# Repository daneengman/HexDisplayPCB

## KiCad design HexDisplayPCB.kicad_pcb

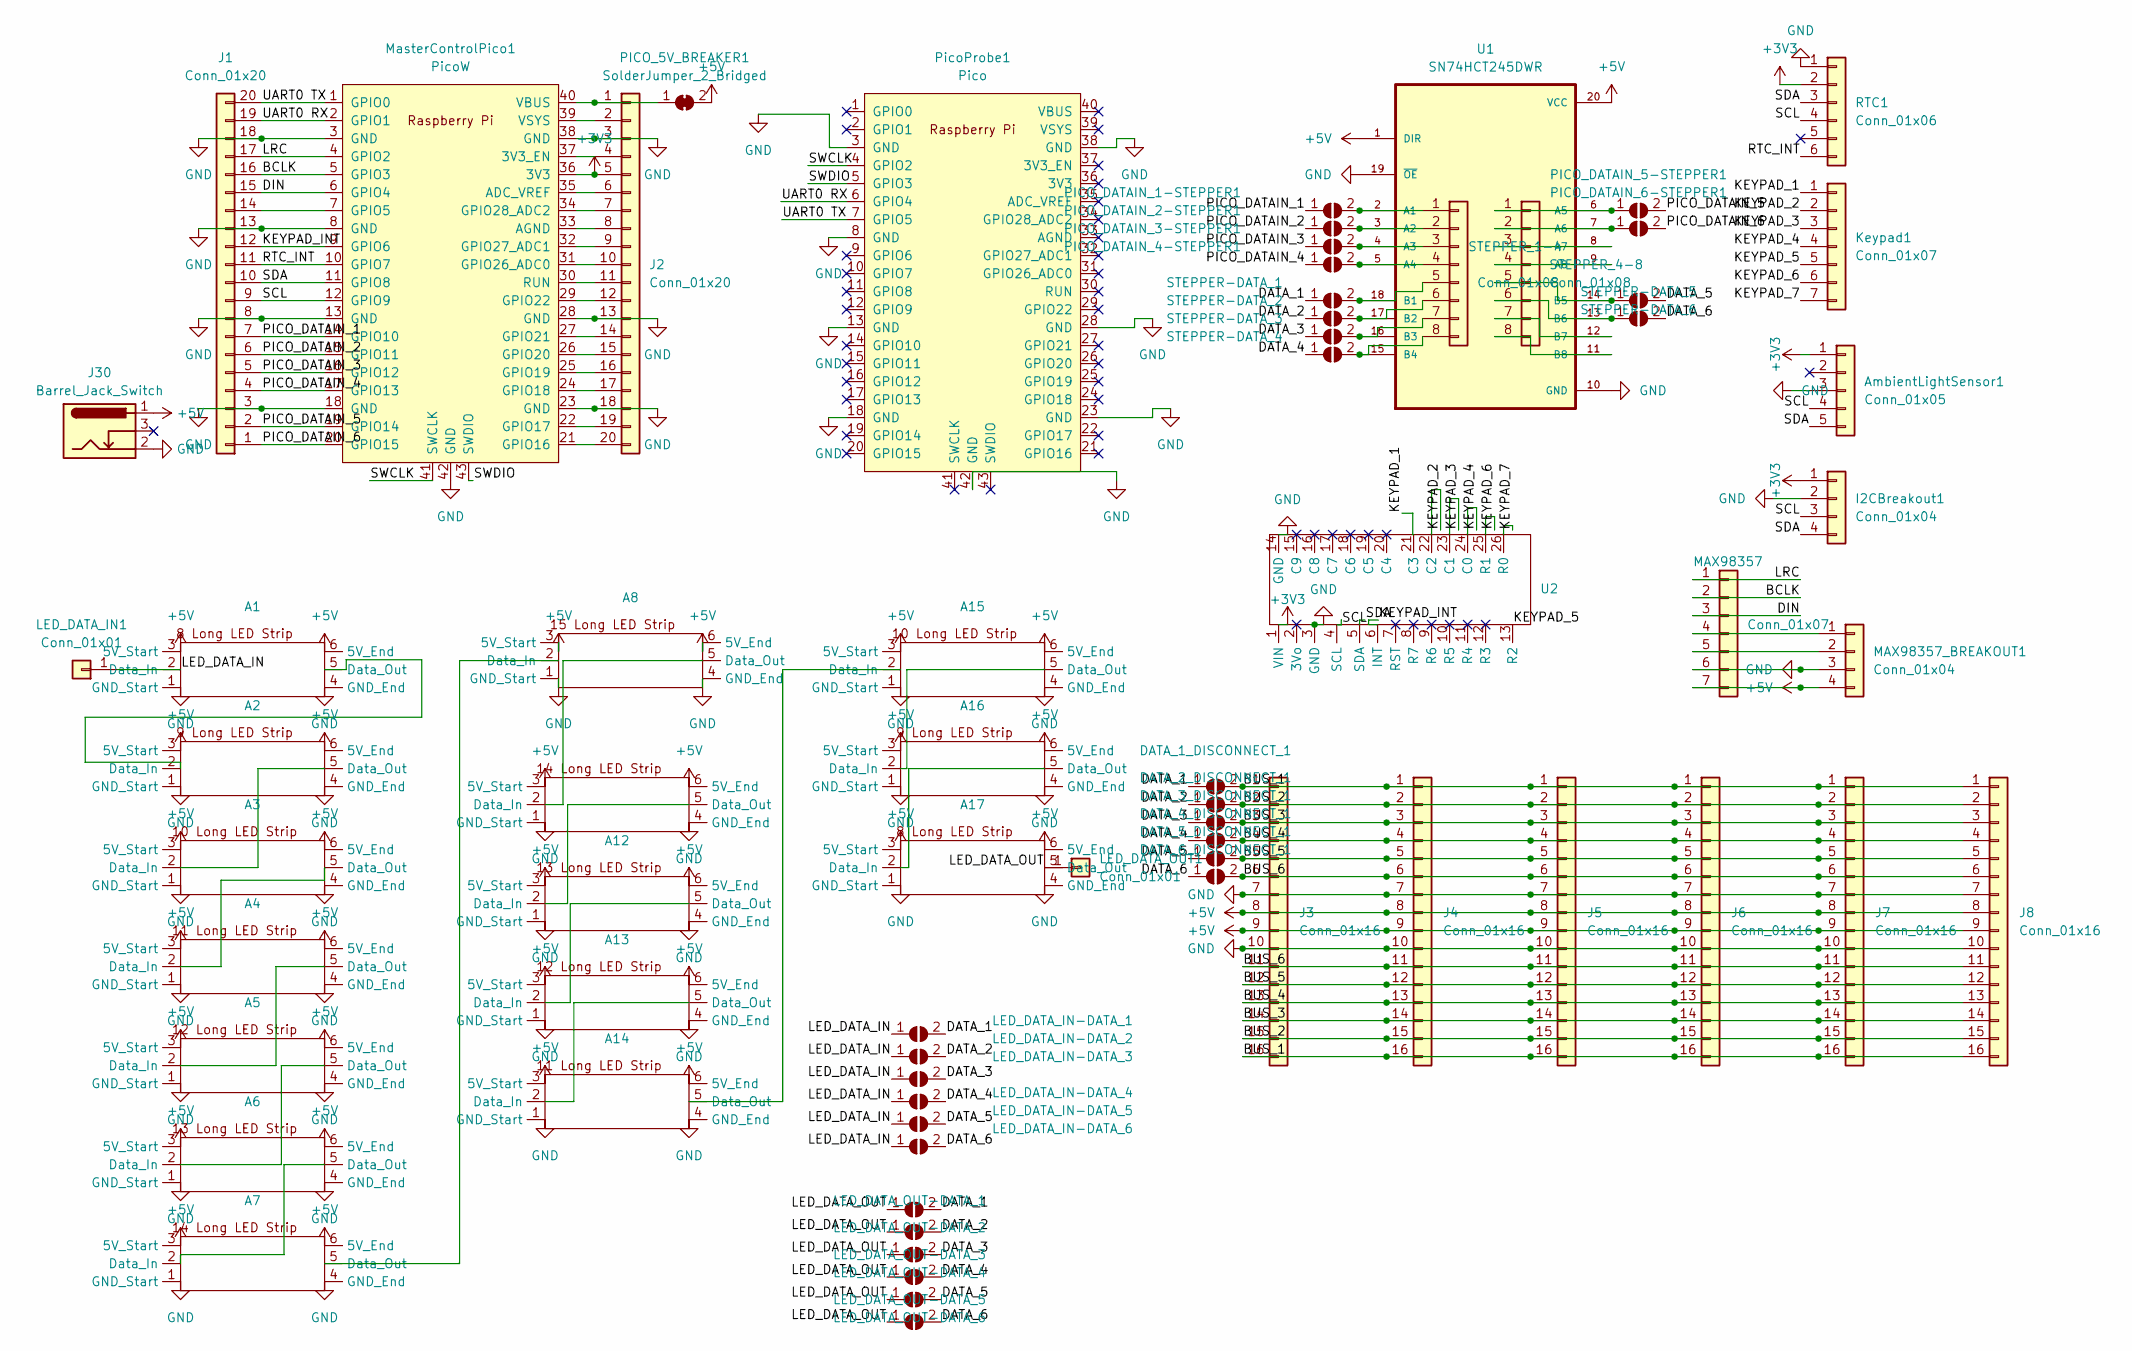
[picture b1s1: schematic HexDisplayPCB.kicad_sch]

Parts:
A1, A17: 8_Long_Standard
A2, A16: 9_Long_Standard
A3, A15: 10_Long_Standard
A4, A14: 11_Long_Standard
A5, A13: 12_Long_Standard
A6, A12: 13_Long_Standard
A7, A11: 14_Long_Standard
A8: 15_Long_Standard
AmbientLightSensor1: Conn_01x05; PinHeader_1x05_P2.54mm_Vertical
DATA_1_DISCONNECT_1, DATA_2_DISCONNECT_1, DATA_3_DISCONNECT_1, DATA_4_DISCONNECT_1, DATA_5_DISCONNECT_1, DATA_6_DISCONNECT_1: SolderJumper_2_Open; SolderJumper-2_P1.3mm_Open_TrianglePad1.0x1.5mm
I2CBreakout1: Conn_01x04; PinSocket_1x04_P2.54mm_Vertical
J1, J2: Conn_01x20; PinSocket_1x20_P2.54mm_Vertical
J3, J4, J5, J6, J7, J8: Conn_01x16; PinHeader_1x16_P2.54mm_Vertical
J30: Barrel_Jack_Switch; BarrelJack_Horizontal
Keypad1: Conn_01x07; PinHeader_1x07_P2.54mm_Vertical
LED_DATA_IN1: Conn_01x01; PinSocket_1x01_P2.54mm_Vertical
LED_DATA_IN-DATA_1, LED_DATA_IN-DATA_2, LED_DATA_IN-DATA_3, LED_DATA_IN-DATA_4, LED_DATA_IN-DATA_5, LED_DATA_IN-DATA_6: SolderJumper_2_Open; SolderJumper-2_P1.3mm_Open_TrianglePad1.0x1.5mm
LED_DATA_OUT1: Conn_01x01; PinSocket_1x01_P2.54mm_Vertical
LED_DATA_OUT-DATA_1, LED_DATA_OUT-DATA_2, LED_DATA_OUT-DATA_3, LED_DATA_OUT-DATA_4, LED_DATA_OUT-DATA_5, LED_DATA_OUT-DATA_6: SolderJumper_2_Open; SolderJumper-2_P1.3mm_Open_TrianglePad1.0x1.5mm
MAX98357: Conn_01x07; PinHeader_1x07_P2.54mm_Vertical
MAX98357_BREAKOUT1: Conn_01x04; PinSocket_1x04_P2.54mm_Vertical
MasterControlPico1: PicoW; RPi_PicoW_SMD_TH
PICO_5V_BREAKER1: SolderJumper_2_Bridged; SolderJumper-2_P1.3mm_Bridged_Pad1.0x1.5mm
PICO_DATAIN_1-STEPPER1, PICO_DATAIN_2-STEPPER1, PICO_DATAIN_3-STEPPER1, PICO_DATAIN_4-STEPPER1, PICO_DATAIN_5-STEPPER1, PICO_DATAIN_6-STEPPER1: SolderJumper_2_Open; SolderJumper-2_P1.3mm_Open_TrianglePad1.0x1.5mm
PicoProbe1: Pico; RPi_Pico_SMD_TH
RTC1: Conn_01x06; PinHeader_1x06_P2.54mm_Vertical
STEPPER-DATA_1, STEPPER-DATA_2, STEPPER-DATA_3, STEPPER-DATA_4, STEPPER-DATA_5, STEPPER-DATA_6: SolderJumper_2_Open; SolderJumper-2_P1.3mm_Open_TrianglePad1.0x1.5mm
STEPPER_1-4, STEPPER_4-8: Conn_01x08; PinHeader_1x08_P2.54mm_Vertical
U1: SN74HCT245DWR; DIP794W45P254L2540H508Q20
U2: TCA8418

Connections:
+3V3: AmbientLightSensor1.1, I2CBreakout1.1, J2.5, MasterControlPico1.36 (3V3), RTC1.2, U2.1 (VIN)
+5V: A1.3 (5V_Start), A1.6 (5V_End), A2.3 (5V_Start), A2.6 (5V_End), A3.3 (5V_Start), A3.6 (5V_End), A4.3 (5V_Start), A4.6 (5V_End), A5.3 (5V_Start), A5.6 (5V_End), A6.3 (5V_Start), A6.6 (5V_End), A7.3 (5V_Start), A7.6 (5V_End), A8.3 (5V_Start), A8.6 (5V_End), A11.3 (5V_Start), A11.6 (5V_End), A12.3 (5V_Start), A12.6 (5V_End), A13.3 (5V_Start), A13.6 (5V_End), A14.3 (5V_Start), A14.6 (5V_End), A15.3 (5V_Start), A15.6 (5V_End), A16.3 (5V_Start), A16.6 (5V_End), A17.3 (5V_Start), A17.6 (5V_End), J3.8, J3.9, J4.8, J4.9, J5.8, J5.9, J6.8, J6.9, J7.8, J7.9, J8.8, J8.9, J30.1, MAX98357.7, MAX98357_BREAKOUT1.4, PICO_5V_BREAKER1.2 (B), U1.1 (DIR), U1.20 (VCC)
/BCLK: J1.16, MAX98357.2, MasterControlPico1.5 (GPIO3)
/BUS_1: DATA_1_DISCONNECT_1.2 (B), J3.1, J3.16, J4.1, J4.16, J5.1, J5.16, J6.1, J6.16, J7.1, J7.16, J8.1, J8.16
/BUS_2: DATA_2_DISCONNECT_1.2 (B), J3.2, J3.15, J4.2, J4.15, J5.2, J5.15, J6.2, J6.15, J7.2, J7.15, J8.2, J8.15
/BUS_3: DATA_3_DISCONNECT_1.2 (B), J3.3, J3.14, J4.3, J4.14, J5.3, J5.14, J6.3, J6.14, J7.3, J7.14, J8.3, J8.14
/BUS_4: DATA_4_DISCONNECT_1.2 (B), J3.4, J3.13, J4.4, J4.13, J5.4, J5.13, J6.4, J6.13, J7.4, J7.13, J8.4, J8.13
/BUS_5: DATA_5_DISCONNECT_1.2 (B), J3.5, J3.12, J4.5, J4.12, J5.5, J5.12, J6.5, J6.12, J7.5, J7.12, J8.5, J8.12
/BUS_6: DATA_6_DISCONNECT_1.2 (B), J3.6, J3.11, J4.6, J4.11, J5.6, J5.11, J6.6, J6.11, J7.6, J7.11, J8.6, J8.11
/DATA_1: DATA_1_DISCONNECT_1.1 (A), LED_DATA_IN-DATA_1.2 (B), LED_DATA_OUT-DATA_1.2 (B), STEPPER-DATA_1.1 (A)
/DATA_2: DATA_2_DISCONNECT_1.1 (A), LED_DATA_IN-DATA_2.2 (B), LED_DATA_OUT-DATA_2.2 (B), STEPPER-DATA_2.1 (A)
/DATA_3: DATA_3_DISCONNECT_1.1 (A), LED_DATA_IN-DATA_3.2 (B), LED_DATA_OUT-DATA_3.2 (B), STEPPER-DATA_3.1 (A)
/DATA_4: DATA_4_DISCONNECT_1.1 (A), LED_DATA_IN-DATA_4.2 (B), LED_DATA_OUT-DATA_4.2 (B), STEPPER-DATA_4.1 (A)
/DATA_5: DATA_5_DISCONNECT_1.1 (A), LED_DATA_IN-DATA_5.2 (B), LED_DATA_OUT-DATA_5.2 (B), STEPPER-DATA_5.2 (B)
/DATA_6: DATA_6_DISCONNECT_1.1 (A), LED_DATA_IN-DATA_6.2 (B), LED_DATA_OUT-DATA_6.2 (B), STEPPER-DATA_6.2 (B)
/DIN: J1.15, MAX98357.3, MasterControlPico1.6 (GPIO4)
/KEYPAD_1: Keypad1.1, U2.21 (C3)
/KEYPAD_2: Keypad1.2, U2.22 (C2)
/KEYPAD_3: Keypad1.3, U2.23 (C1)
/KEYPAD_4: Keypad1.4, U2.24 (C0)
/KEYPAD_5: Keypad1.5, U2.13 (R2)
/KEYPAD_6: Keypad1.6, U2.25 (R1)
/KEYPAD_7: Keypad1.7, U2.26 (R0)
/KEYPAD_INT: J1.12, MasterControlPico1.9 (GPIO6), U2.6 (INT)
/LED_DATA_IN: A1.2 (Data_In), LED_DATA_IN1.1, LED_DATA_IN-DATA_1.1 (A), LED_DATA_IN-DATA_2.1 (A), LED_DATA_IN-DATA_3.1 (A), LED_DATA_IN-DATA_4.1 (A), LED_DATA_IN-DATA_5.1 (A), LED_DATA_IN-DATA_6.1 (A)
/LED_DATA_OUT: A17.5 (Data_Out), LED_DATA_OUT1.1, LED_DATA_OUT-DATA_1.1 (A), LED_DATA_OUT-DATA_2.1 (A), LED_DATA_OUT-DATA_3.1 (A), LED_DATA_OUT-DATA_4.1 (A), LED_DATA_OUT-DATA_5.1 (A), LED_DATA_OUT-DATA_6.1 (A)
/LRC: J1.17, MAX98357.1, MasterControlPico1.4 (GPIO2)
/PICO_DATAIN_1: J1.7, MasterControlPico1.14 (GPIO10), PICO_DATAIN_1-STEPPER1.1 (A)
/PICO_DATAIN_2: J1.6, MasterControlPico1.15 (GPIO11), PICO_DATAIN_2-STEPPER1.1 (A)
/PICO_DATAIN_3: J1.5, MasterControlPico1.16 (GPIO12), PICO_DATAIN_3-STEPPER1.1 (A)
/PICO_DATAIN_4: J1.4, MasterControlPico1.17 (GPIO13), PICO_DATAIN_4-STEPPER1.1 (A)
/PICO_DATAIN_5: J1.2, MasterControlPico1.19 (GPIO14), PICO_DATAIN_5-STEPPER1.2 (B)
/PICO_DATAIN_6: J1.1, MasterControlPico1.20 (GPIO15), PICO_DATAIN_6-STEPPER1.2 (B)
/RTC_INT: J1.11, MasterControlPico1.10 (GPIO7), RTC1.6
/SCL: AmbientLightSensor1.4, I2CBreakout1.3, J1.9, MasterControlPico1.12 (GPIO9), RTC1.4, U2.4 (SCL)
/SDA: AmbientLightSensor1.5, I2CBreakout1.4, J1.10, MasterControlPico1.11 (GPIO8), RTC1.3, U2.5 (SDA)
/SWCLK: MasterControlPico1.41 (SWCLK), PicoProbe1.4 (GPIO2)
/SWDIO: MasterControlPico1.43 (SWDIO), PicoProbe1.5 (GPIO3)
/UART0 RX: J1.19, MasterControlPico1.2 (GPIO1), PicoProbe1.6 (GPIO4)
/UART0 TX: J1.20, MasterControlPico1.1 (GPIO0), PicoProbe1.7 (GPIO5)
GND: A1.1 (GND_Start), A1.4 (GND_End), A2.1 (GND_Start), A2.4 (GND_End), A3.1 (GND_Start), A3.4 (GND_End), A4.1 (GND_Start), A4.4 (GND_End), A5.1 (GND_Start), A5.4 (GND_End), A6.1 (GND_Start), A6.4 (GND_End), A7.1 (GND_Start), A7.4 (GND_End), A8.1 (GND_Start), A8.4 (GND_End), A11.1 (GND_Start), A11.4 (GND_End), A12.1 (GND_Start), A12.4 (GND_End), A13.1 (GND_Start), A13.4 (GND_End), A14.1 (GND_Start), A14.4 (GND_End), A15.1 (GND_Start), A15.4 (GND_End), A16.1 (GND_Start), A16.4 (GND_End), A17.1 (GND_Start), A17.4 (GND_End), AmbientLightSensor1.3, I2CBreakout1.2, J1.3, J1.8, J1.13, J1.18, J2.3, J2.13, J2.18, J3.7, J3.10, J4.7, J4.10, J5.7, J5.10, J6.7, J6.10, J7.7, J7.10, J8.7, J8.10, J30.2, MAX98357.6, MAX98357_BREAKOUT1.3, MasterControlPico1.3 (GND), MasterControlPico1.8 (GND), MasterControlPico1.13 (GND), MasterControlPico1.18 (GND), MasterControlPico1.23 (GND), MasterControlPico1.28 (GND), MasterControlPico1.38 (GND), MasterControlPico1.42 (GND), PicoProbe1.3 (GND), PicoProbe1.8 (GND), PicoProbe1.13 (GND), PicoProbe1.18 (GND), PicoProbe1.23 (GND), PicoProbe1.28 (GND), PicoProbe1.38 (GND), PicoProbe1.42 (GND), RTC1.1, U1.10 (GND), U1.19 (~OE), U2.3 (GND), U2.14 (GND)
unnamed: A1.5 (Data_Out), A2.2 (Data_In)
unnamed: A2.5 (Data_Out), A3.2 (Data_In)
unnamed: A3.5 (Data_Out), A4.2 (Data_In)
unnamed: A4.5 (Data_Out), A5.2 (Data_In)
unnamed: A5.5 (Data_Out), A6.2 (Data_In)
unnamed: A6.5 (Data_Out), A7.2 (Data_In)
unnamed: A7.5 (Data_Out), A8.2 (Data_In)
unnamed: A8.5 (Data_Out), A11.2 (Data_In)
unnamed: A11.5 (Data_Out), A12.2 (Data_In)
unnamed: A12.5 (Data_Out), A13.2 (Data_In)
unnamed: A13.5 (Data_Out), A14.2 (Data_In)
unnamed: A14.5 (Data_Out), A15.2 (Data_In)
unnamed: A15.5 (Data_Out), A16.2 (Data_In)
unnamed: A16.5 (Data_Out), A17.2 (Data_In)
unnamed: J1.14, MasterControlPico1.7 (GPIO5)
unnamed: J2.1, MasterControlPico1.40 (VBUS), PICO_5V_BREAKER1.1 (A)
unnamed: J2.2, MasterControlPico1.39 (VSYS)
unnamed: J2.4, MasterControlPico1.37 (3V3_EN)
unnamed: J2.6, MasterControlPico1.35 (ADC_VREF)
unnamed: J2.7, MasterControlPico1.34 (GPIO28_ADC2)
unnamed: J2.8, MasterControlPico1.33 (AGND)
unnamed: J2.9, MasterControlPico1.32 (GPIO27_ADC1)
unnamed: J2.10, MasterControlPico1.31 (GPIO26_ADC0)
unnamed: J2.11, MasterControlPico1.30 (RUN)
unnamed: J2.12, MasterControlPico1.29 (GPIO22)
unnamed: J2.14, MasterControlPico1.27 (GPIO21)
unnamed: J2.15, MasterControlPico1.26 (GPIO20)
unnamed: J2.16, MasterControlPico1.25 (GPIO19)
unnamed: J2.17, MasterControlPico1.24 (GPIO18)
unnamed: J2.19, MasterControlPico1.22 (GPIO17)
unnamed: J2.20, MasterControlPico1.21 (GPIO16)
unnamed: MAX98357.4, MAX98357_BREAKOUT1.1
unnamed: MAX98357.5, MAX98357_BREAKOUT1.2
unnamed: PICO_DATAIN_1-STEPPER1.2 (B), STEPPER_1-4.1, U1.2 (A1)
unnamed: PICO_DATAIN_2-STEPPER1.2 (B), STEPPER_1-4.2, U1.3 (A2)
unnamed: PICO_DATAIN_3-STEPPER1.2 (B), STEPPER_1-4.3, U1.4 (A3)
unnamed: PICO_DATAIN_4-STEPPER1.2 (B), STEPPER_1-4.4, U1.5 (A4)
unnamed: PICO_DATAIN_5-STEPPER1.1 (A), STEPPER_4-8.1, U1.6 (A5)
unnamed: PICO_DATAIN_6-STEPPER1.1 (A), STEPPER_4-8.2, U1.7 (A6)
unnamed: STEPPER-DATA_1.2 (B), STEPPER_1-4.5, U1.18 (B1)
unnamed: STEPPER-DATA_2.2 (B), STEPPER_1-4.6, U1.17 (B2)
unnamed: STEPPER-DATA_3.2 (B), STEPPER_1-4.7, U1.16 (B3)
unnamed: STEPPER-DATA_4.2 (B), STEPPER_1-4.8, U1.15 (B4)
unnamed: STEPPER-DATA_5.1 (A), STEPPER_4-8.5, U1.14 (B5)
unnamed: STEPPER-DATA_6.1 (A), STEPPER_4-8.6, U1.13 (B6)
unnamed: STEPPER_4-8.3, U1.8 (A7)
unnamed: STEPPER_4-8.4, U1.9 (A8)
unnamed: STEPPER_4-8.7, U1.12 (B7)
unnamed: STEPPER_4-8.8, U1.11 (B8)

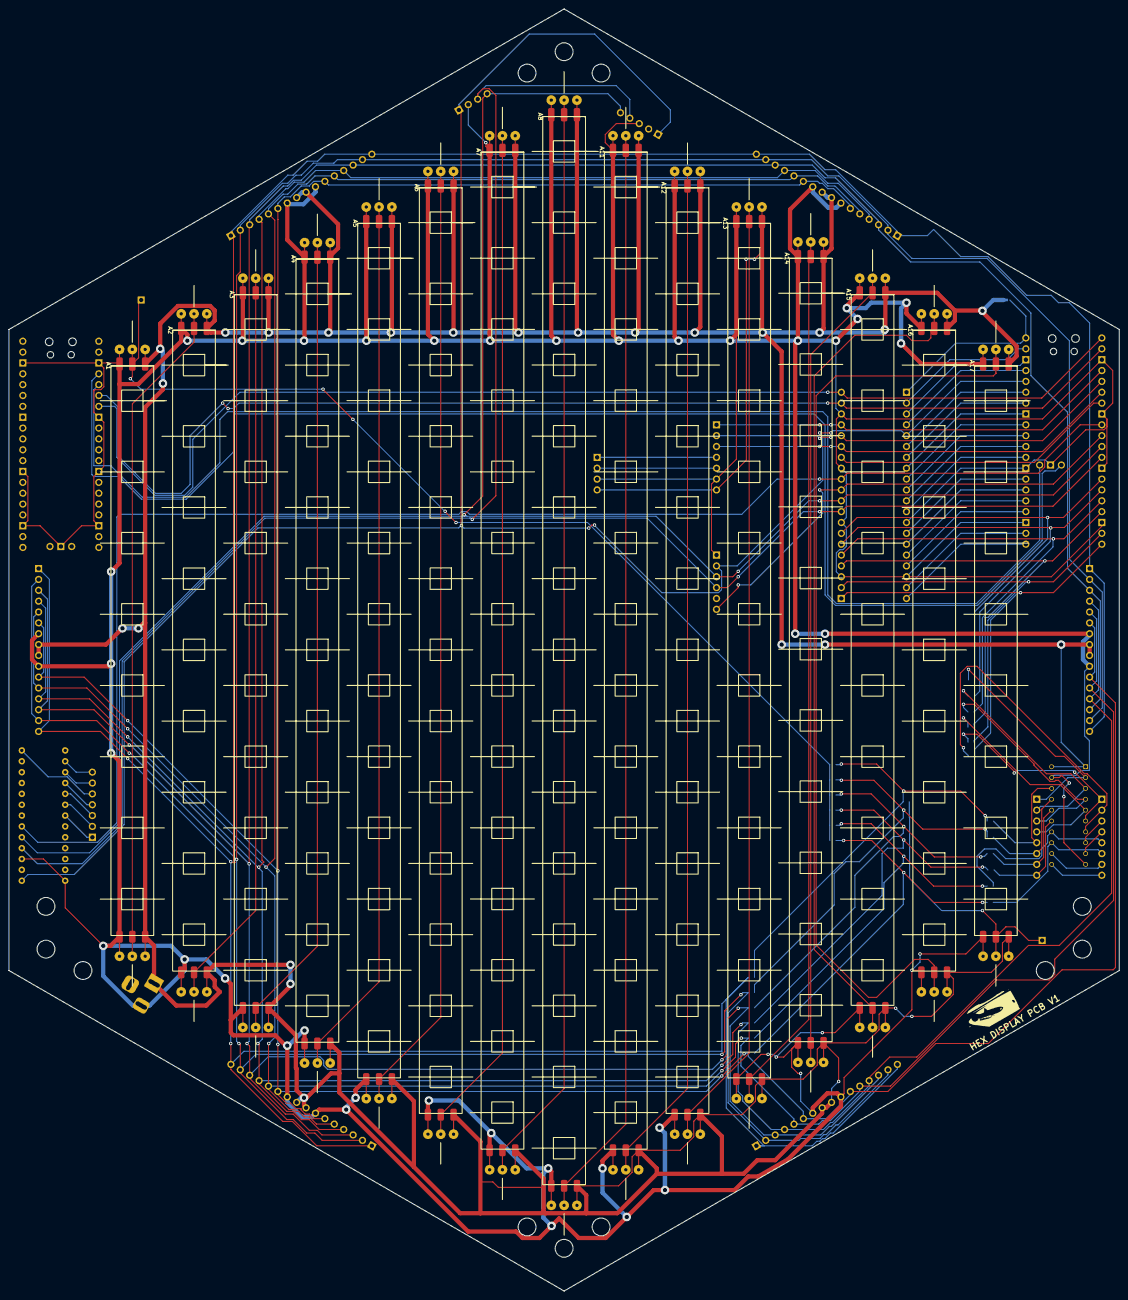
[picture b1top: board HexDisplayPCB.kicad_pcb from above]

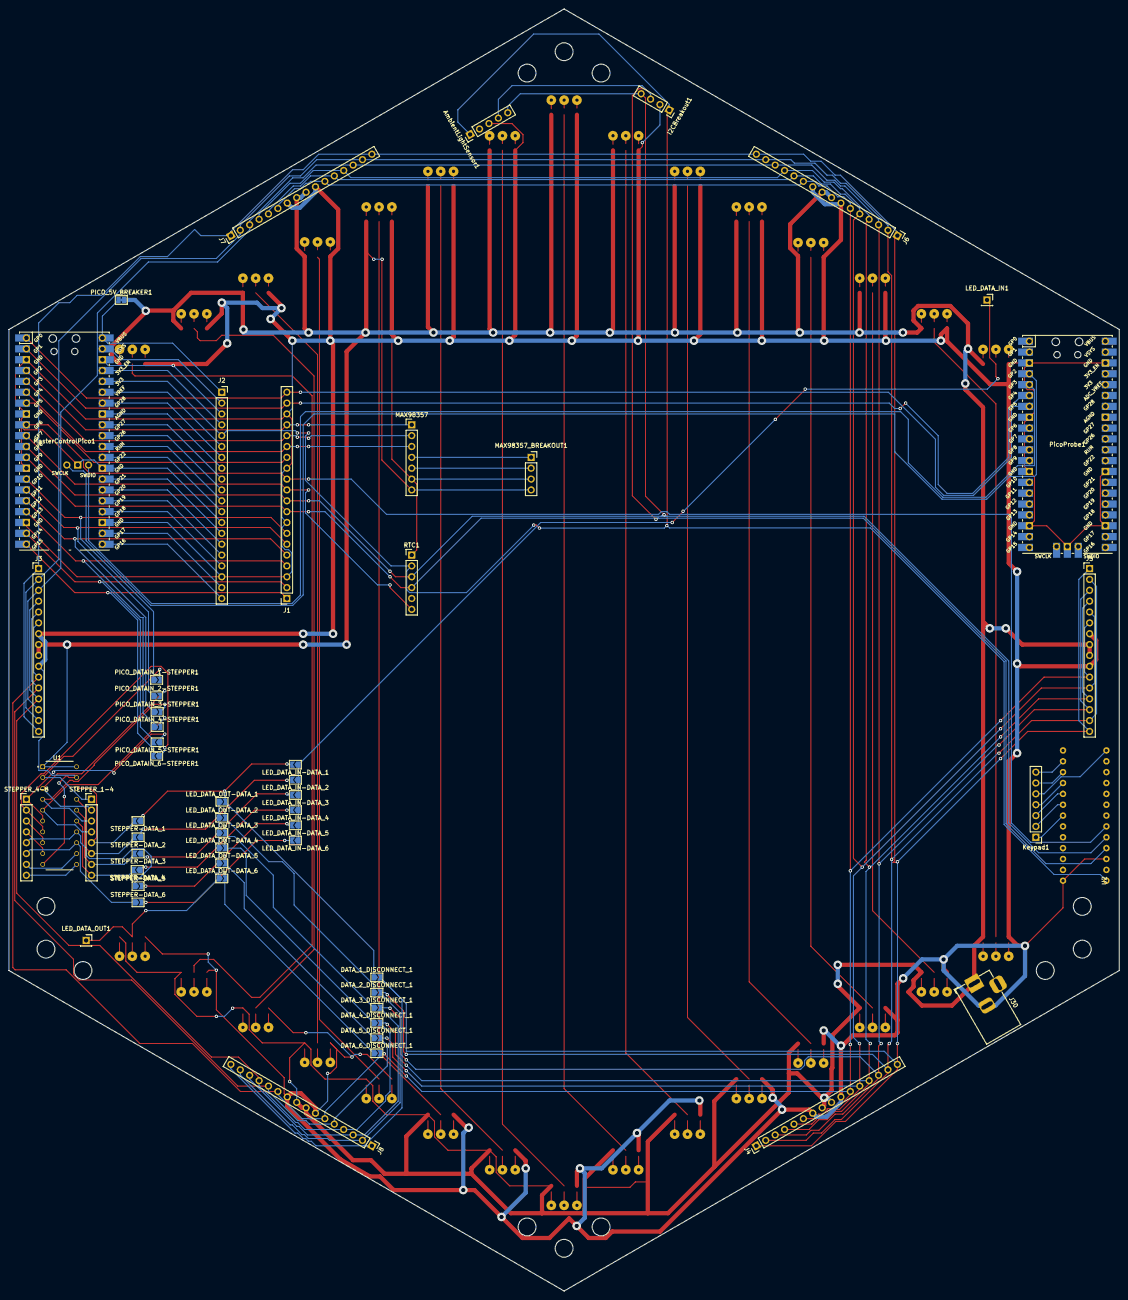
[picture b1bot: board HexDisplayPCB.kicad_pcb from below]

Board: 2 copper layers, 259.8 x 300.0 mm, 69 parts (54 on the bottom side), 90 nets.

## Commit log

2023-12-30 Adds schematics for strips
2024-01-02 A lot more is in the schematic
2024-01-04 Draft 1 of layout
2024-01-04 Final first draft with gerber
2024-01-08 Final image adjustments
